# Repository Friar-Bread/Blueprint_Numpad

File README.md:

# Blueprint_Numpad

This numpad is to use for CAD and other programs that use number entry a lot.
I like my smaller keyboard but I often wish I had a numpad which is where this comes in.
I'm using a 4 by 6 layout which is fairly basic but it doesn't have the larger keys that some have.

CAD

[Onshape Link](https://cad.onshape.com/documents/a49eb517829c44ded4fb0486/w/c1ab92566ff330dc74a4adf9/e/f54a2c3f6400f8bab8c2b79a?renderMode=0&uiState=695007a653e645a863be166c)

Schematic 

PCB

BOM
| Item           | Quant. Needed | Order Quant. | Price  | Link                                                                                                                                                                                                                                                                                                                                                                                                                                                                                                                                                                                                                                                                                                                                                                                                                                                                                                                                                                                                                                                                                                                                                                                                                                                                                                                                           |
| -------------- | ------------- | ------------ | ------ | ---------------------------------------------------------------------------------------------------------------------------------------------------------------------------------------------------------------------------------------------------------------------------------------------------------------------------------------------------------------------------------------------------------------------------------------------------------------------------------------------------------------------------------------------------------------------------------------------------------------------------------------------------------------------------------------------------------------------------------------------------------------------------------------------------------------------------------------------------------------------------------------------------------------------------------------------------------------------------------------------------------------------------------------------------------------------------------------------------------------------------------------------------------------------------------------------------------------------------------------------------------------------------------------------------------------------------------------------- |
| PCB | 1 | 5 | $17.43 | JLC PCB
| nRF52840       | 1             | 1            | $9.99  | [link](https://www.seeedstudio.com/Seeed-XIAO-BLE-nRF52840-p-5201.html?srsltid=AfmBOooNVJRtJbW0_-sioOdgaC2nRMISnjG38KtNPB509mUfPgTSD2YQ)    |
|Shipping | | | $6.20
| Keycaps        | 24            | 24           | $0.00  | 3D printing    |
| Diodes         | 24            | 100          | $1.35  | [link](https://www.aliexpress.us/item/3256801808479789.html?)    |
| Battery        | 1             | 1            | $11.79 | [link](https://www.aliexpress.us/item/3256809787664995.html)      |
| Shipping       |               |              | $5.46  |    |
| Key Switches   | 24            | 40           | $7.08	| [link](https://www.aliexpress.us/item/3256802192387196.html ) |
| 806K Resistor  | 1             | 5            | $0.50  | [link](https://www.digikey.com/en/products/detail/yageo/RC0805FR-07806KL/728163?_gl=1*4gvh37*_up*MQ..*_gs*MQ..&gclid=Cj0KCQiApL7KBhC7ARIsAD2Xq3BnetevqobDLaJXFequbegAI4TZ99Bg5tDC2t5AI5cwf-Y5ro517YwaAmoDEALw_wcB&gclsrc=aw.ds&gbraid=0AAAAADrbLli4t4EHTCttVpMlLiA4DVNdA)    |
| 2M Resistor    | 1             | 5            | $0.90  | [link](https://www.digikey.com/en/products/detail/te-connectivity-passive-product/CPF0805B2M0E/4966423?_gl=1*11z9isq*_up*MQ..*_gs*MQ..&gclid=Cj0KCQiApL7KBhC7ARIsAD2Xq3BnetevqobDLaJXFequbegAI4TZ99Bg5tDC2t5AI5cwf-Y5ro517YwaAmoDEALw_wcB&gclsrc=aw.ds&gbraid=0AAAAADrbLli4t4EHTCttVpMlLiA4DVNdA)               |
| Shipping       |               |              | $4.99  |      |
| Total          |               |              | $76.06 |   |
| Total with tax |               |              | $81.38 |     |

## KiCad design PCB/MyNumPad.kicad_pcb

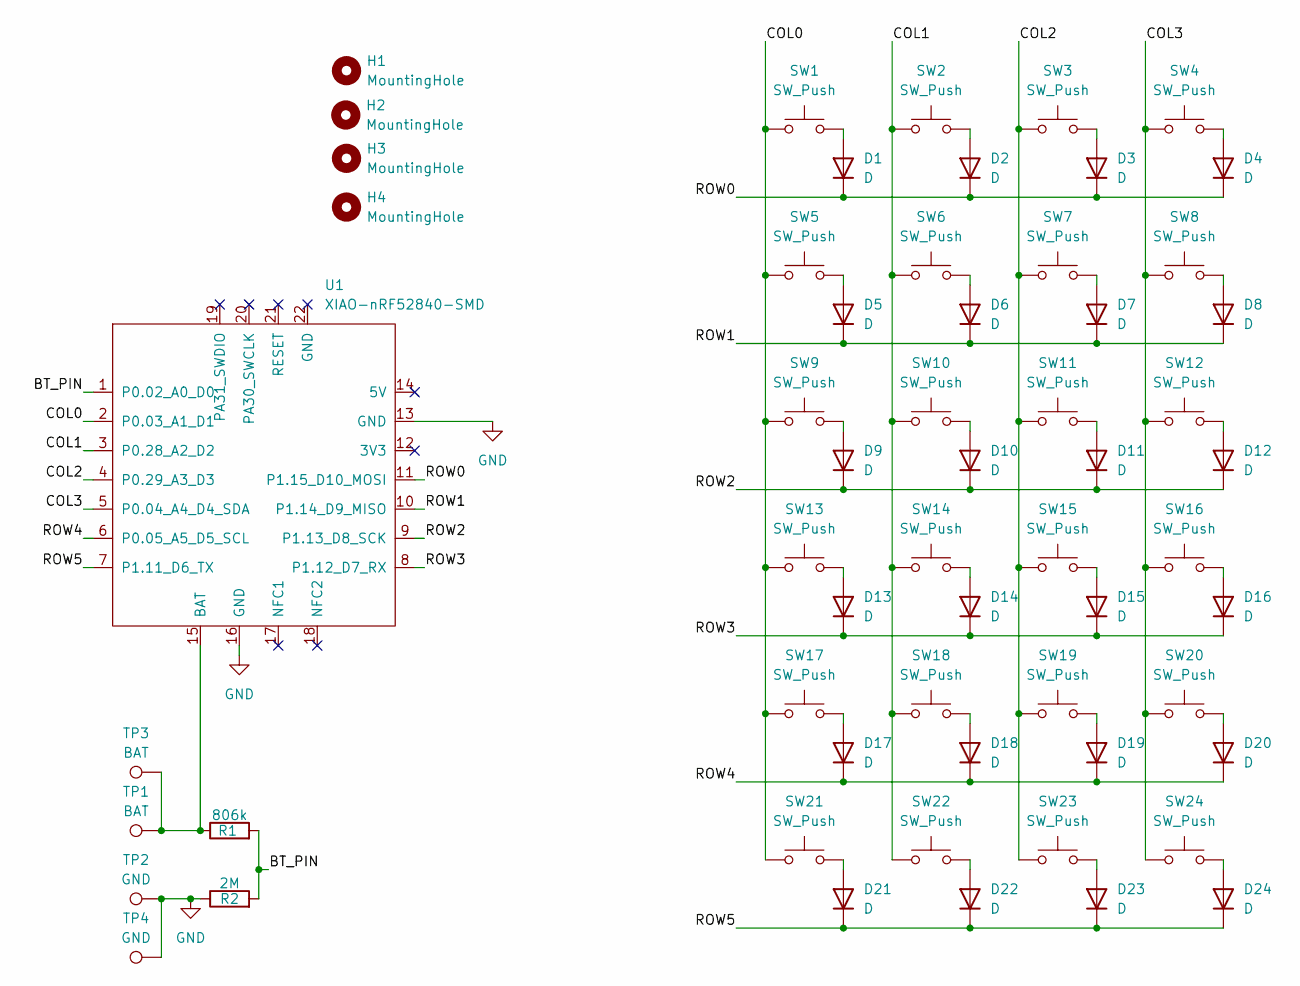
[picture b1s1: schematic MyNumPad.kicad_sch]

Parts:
D1, D2, D3, D4, D5, D6, D7, D8, D9, D10, D11, D12, D13, D14, D15, D16, D17, D18, D19, D20, D21, D22, D23, D24: D; D_SOD-123
H1, H2, H3, H4: MountingHole; MountingHole_4mm
R1: 806k; R_0805_2012Metric
R2: 2M; R_0805_2012Metric
SW1, SW2, SW3, SW4, SW5, SW6, SW7, SW8, SW9, SW10, SW11, SW12, SW13, SW14, SW15, SW16, SW17, SW18, SW19, SW20, SW21, SW22, SW23, SW24: SW_Push; SW_MX_1u
TP1, TP3: BAT; TestPoint_Pad_D2.0mm
TP2, TP4: GND; TestPoint_Pad_D2.0mm
U1: XIAO-nRF52840-SMD; modified-XIAO-nRF52840-SMD

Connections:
/BT_PIN: R1.2, R2.2, U1.1 (P0.02_A0_D0)
/COL0: SW1.1, SW5.1, SW9.1, SW13.1, SW17.1, SW21.1, U1.2 (P0.03_A1_D1)
/COL1: SW2.1, SW6.1, SW10.1, SW14.1, SW18.1, SW22.1, U1.3 (P0.28_A2_D2)
/COL2: SW3.1, SW7.1, SW11.1, SW15.1, SW19.1, SW23.1, U1.4 (P0.29_A3_D3)
/COL3: SW4.1, SW8.1, SW12.1, SW16.1, SW20.1, SW24.1, U1.5 (P0.04_A4_D4_SDA)
/ROW0: D1.1 (K), D2.1 (K), D3.1 (K), D4.1 (K), U1.11 (P1.15_D10_MOSI)
/ROW1: D5.1 (K), D6.1 (K), D7.1 (K), D8.1 (K), U1.10 (P1.14_D9_MISO)
/ROW2: D9.1 (K), D10.1 (K), D11.1 (K), D12.1 (K), U1.9 (P1.13_D8_SCK)
/ROW3: D13.1 (K), D14.1 (K), D15.1 (K), D16.1 (K), U1.8 (P1.12_D7_RX)
/ROW4: D17.1 (K), D18.1 (K), D19.1 (K), D20.1 (K), U1.6 (P0.05_A5_D5_SCL)
/ROW5: D21.1 (K), D22.1 (K), D23.1 (K), D24.1 (K), U1.7 (P1.11_D6_TX)
GND: R2.1, TP2.1, TP4.1, U1.13 (GND), U1.16 (GND)
unnamed: D1.2 (A), SW1.2
unnamed: D2.2 (A), SW2.2
unnamed: D3.2 (A), SW3.2
unnamed: D4.2 (A), SW4.2
unnamed: D5.2 (A), SW5.2
unnamed: D6.2 (A), SW6.2
unnamed: D7.2 (A), SW7.2
unnamed: D8.2 (A), SW8.2
unnamed: D9.2 (A), SW9.2
unnamed: D10.2 (A), SW10.2
unnamed: D11.2 (A), SW11.2
unnamed: D12.2 (A), SW12.2
unnamed: D13.2 (A), SW13.2
unnamed: D14.2 (A), SW14.2
unnamed: D15.2 (A), SW15.2
unnamed: D16.2 (A), SW16.2
unnamed: D17.2 (A), SW17.2
unnamed: D18.2 (A), SW18.2
unnamed: D19.2 (A), SW19.2
unnamed: D20.2 (A), SW20.2
unnamed: D21.2 (A), SW21.2
unnamed: D22.2 (A), SW22.2
unnamed: D23.2 (A), SW23.2
unnamed: D24.2 (A), SW24.2
unnamed: R1.1, TP1.1, TP3.1, U1.15 (BAT)

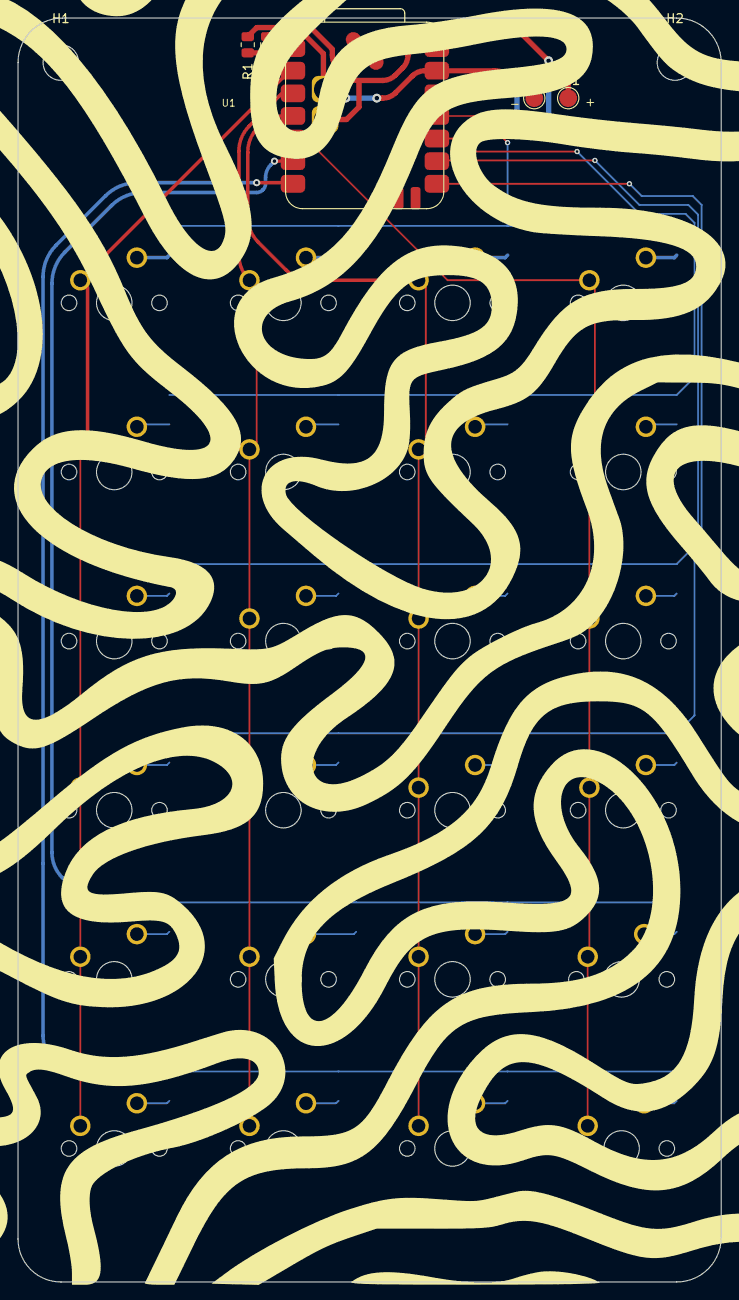
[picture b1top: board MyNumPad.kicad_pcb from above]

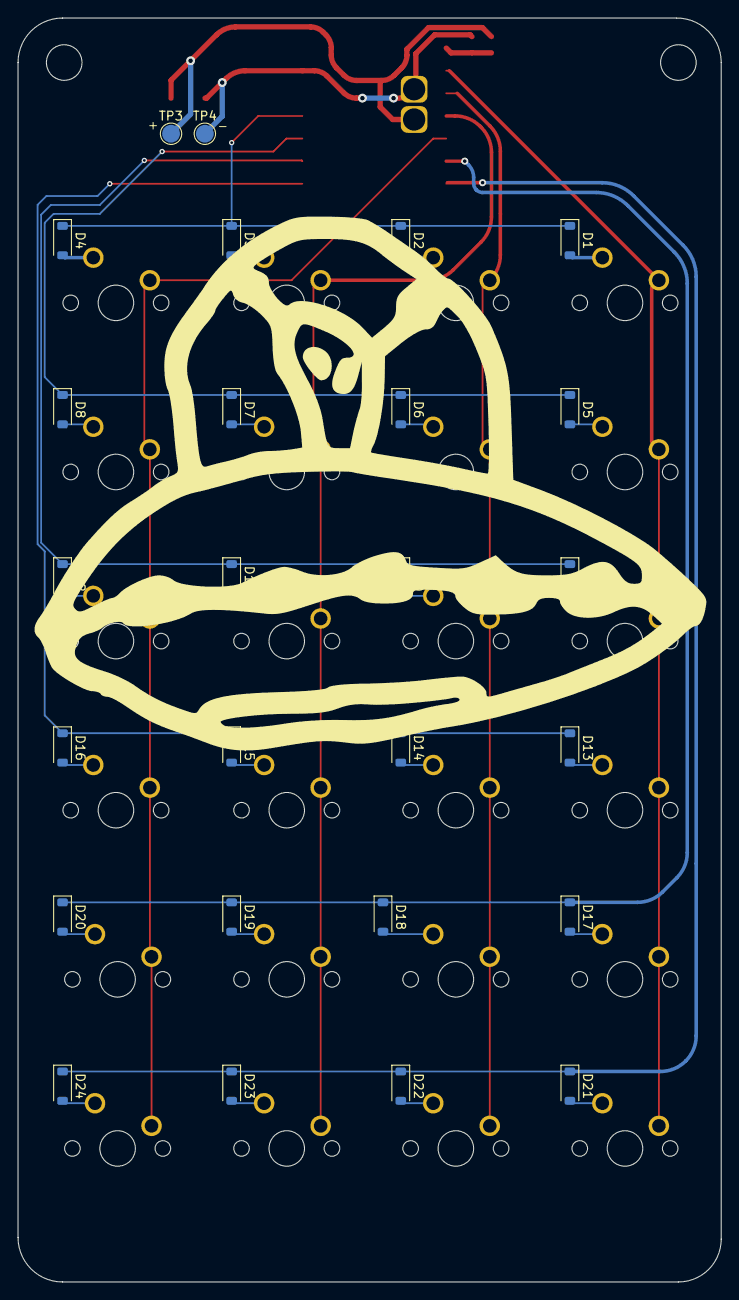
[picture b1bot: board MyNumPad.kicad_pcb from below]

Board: 2 copper layers, 79.0 x 142.0 mm, 57 parts (26 on the bottom side), 37 nets.

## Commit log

2025-12-27 BOM and folders
2025-12-27 added CAD
2025-12-27 PCB stuff
2025-12-27 Images
2025-12-27 firmware added
2025-12-28 updated CAD
2025-12-28 changed schematic image
2025-12-28 update BOM
